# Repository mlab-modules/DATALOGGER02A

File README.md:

# DATALOGGER02A
<!--- LongName --->
## 
<!--- ELongName ---> 

<!--- Lead --->

<!--- ELead --->

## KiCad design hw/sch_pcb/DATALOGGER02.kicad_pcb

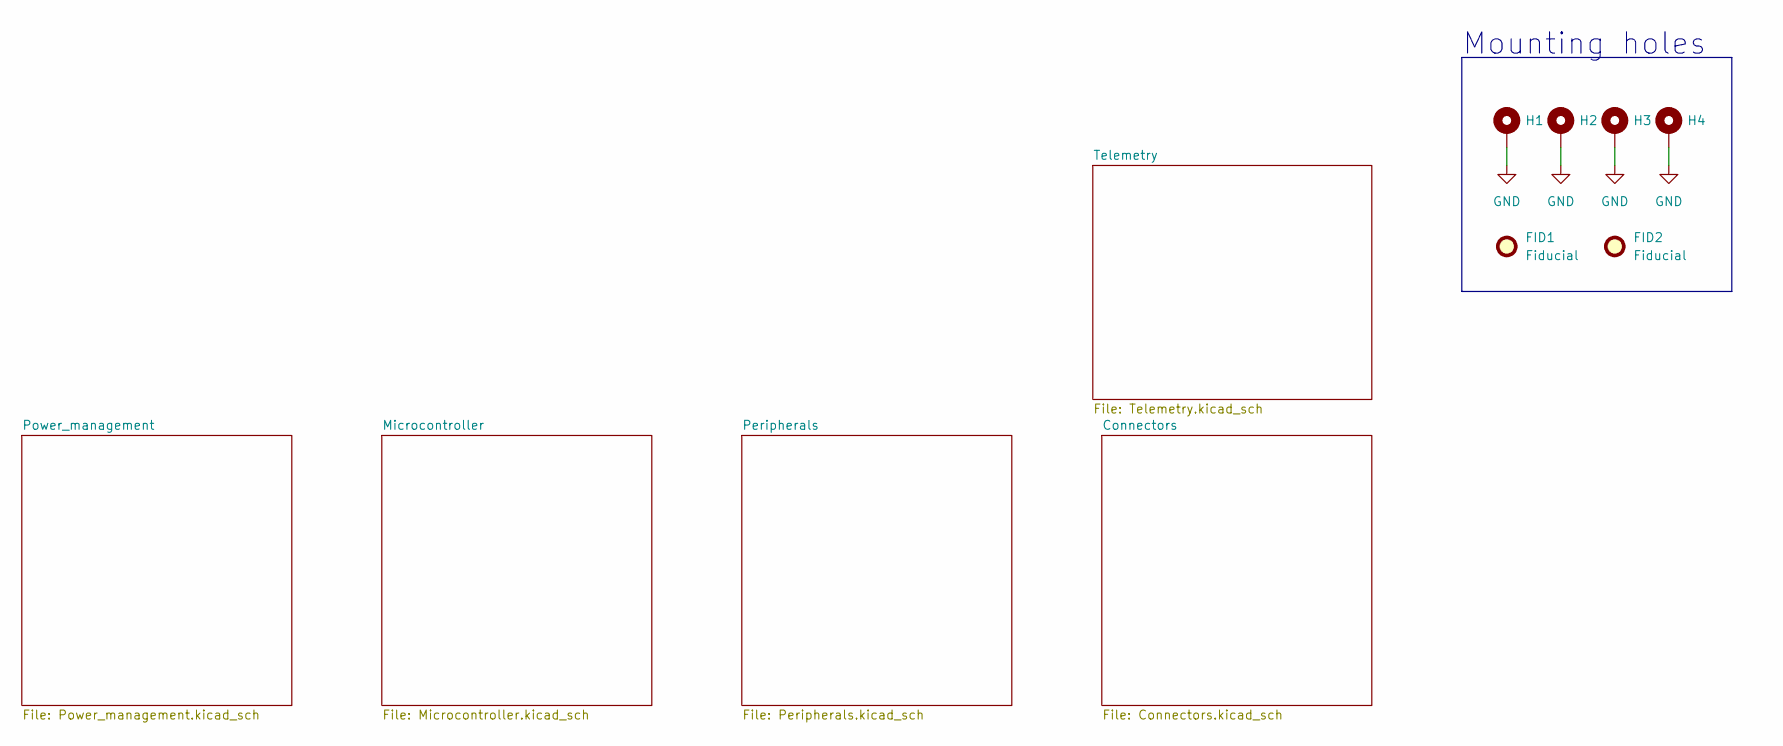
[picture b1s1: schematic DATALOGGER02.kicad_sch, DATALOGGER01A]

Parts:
FID1, FID2: Fiducial; Fiducial_1mm_Mask2mm
H1, H2, H3, H4: MountingHole_Pad; MountingHole_3mm

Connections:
GND: H1.1, H2.1, H3.1, H4.1; also elsewhere on the board

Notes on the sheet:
Mounting holes

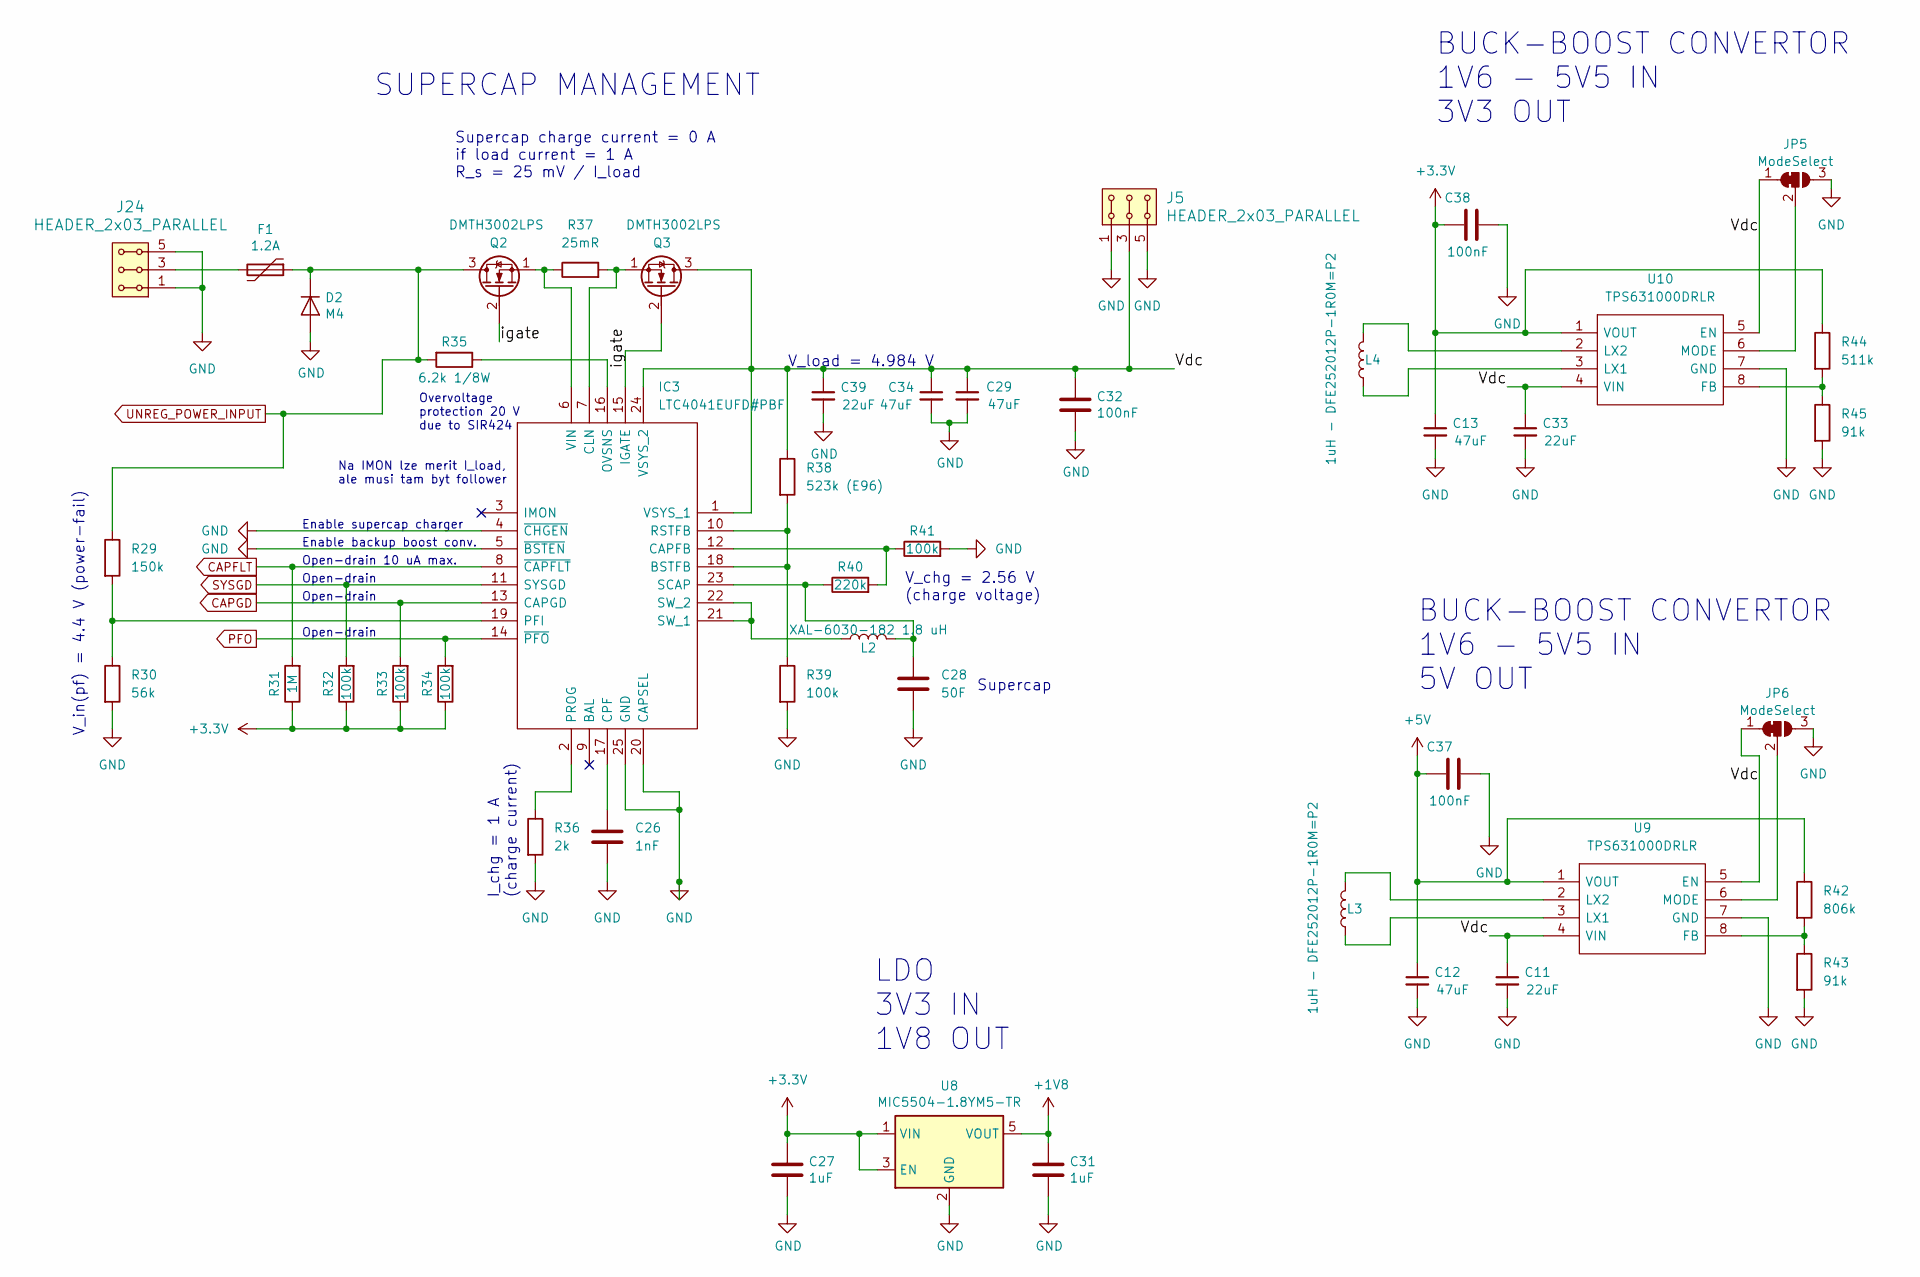
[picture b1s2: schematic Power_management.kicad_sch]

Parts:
C11, C33, C39: 22uF; C_0805_2012Metric
C12, C13, C29, C34: 47uF; C_0805_2012Metric
C26: 1nF; C_0805_2012Metric
C27, C31: 1uF; C_0805_2012Metric
C28: 50F; CP_Radial_D18.0mm_P7.50mm
C32, C37, C38: 100nF; C_0805_2012Metric
D2: M4; Diode-SMA_Standard
F1: 1.2A; 1812
IC3: LTC4041EUFD#PBF; QFN-24-1EP_4x5mm_P0.5mm_EP2.65x3.65mm; Mouser Part Number 584-4041EUFDPB
J5, J24: HEADER_2x03_PARALLEL; Straight_2x03
JP5, JP6: ModeSelect; SolderJumper-3_P1.3mm_Bridged12_RoundedPad1.0x1.5mm_NumberL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
L2: XAL-6030-182 1.8 uH; XAL6030181MEC
L3, L4: 1uH - DFE252012P-1R0M=P2; L_1008_2520Metric
Q2, Q3: DMTH3002LPS; D_POWERDI5060-8_6.0x5.1mm_P1.27mm; Manufacturer_Part_Number DMT31M7LPS-13
R29: 150k; R_0805_2012Metric
R30: 56k; R_0805_2012Metric
R31: 1M; R_0805_2012Metric
R32, R33, R34, R39, R41: 100k; R_0805_2012Metric
R35: 6.2k 1/8W; R_0805_2012Metric
R36: 2k; R_0805_2012Metric
R37: 25mR; R_0805_2012Metric
R38: 523k (E96); R_0805_2012Metric
R40: 220k; R_0805_2012Metric
R42: 806k; R_0805_2012Metric
R43, R45: 91k; R_0805_2012Metric
R44: 511k; R_0805_2012Metric
U8: MIC5504-1.8YM5-TR; SOT-23-5
U9, U10: TPS631000DRLR; SOT-583-8; Mouser Part Number 595-TPS631000DRLR

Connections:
+1V8: C31.1, U8.5 (VOUT); also elsewhere on the board
+3.3V: C13.1, C27.1, C38.1, R31.1, R32.1, R33.1, R34.1, R44.1, U8.1 (VIN), U8.3 (EN), U10.1 (VOUT); also elsewhere on the board
+5V: C12.1, C37.1, R42.1, U9.1 (VOUT); also elsewhere on the board
/Power_management/Vdc: C11.1, C29.1, C32.1, C33.1, C34.1, C39.1, IC3.1 (VSYS_1), IC3.24 (VSYS_2), J5.3, J5.4, JP5.1 (A), JP6.1 (A), Q3.3 (D), R38.1, U9.4 (VIN), U9.5 (EN), U10.4 (VIN), U10.5 (EN)
/Power_management/igate: IC3.15 (IGATE), Q2.2 (G), Q3.2 (G)
CAPFLT: IC3.8 (~CAPFLT), R31.2; also elsewhere on the board
CAPGD: IC3.13 (CAPGD), R33.2; also elsewhere on the board
GND: C11.2, C12.2, C13.2, C26.2, C27.2, C28.2, C29.2, C31.2, C32.2, C33.2, C34.2, C37.2, C38.2, C39.2, D2.2 (A), IC3.4 (~CHGEN), IC3.5 (~BSTEN), IC3.20 (CAPSEL), IC3.25 (GND), J5.1, J5.2, J5.5, J5.6, J24.1, J24.2, J24.5, J24.6, JP5.3 (B), JP6.3 (B), R30.2, R36.2, R39.2, R41.2, R43.2, R45.2, U8.2 (GND), U9.7 (GND), U10.7 (GND); also elsewhere on the board
unnamed: F1.2, J24.3, J24.4
unnamed: IC3.10 (RSTFB), IC3.18 (BSTFB), R38.2, R39.1
unnamed: IC3.12 (CAPFB), R40.2, R41.1
unnamed: IC3.7 (CLN), Q3.1 (S), R37.2
unnamed: C26.1, IC3.17 (CPF)
unnamed: IC3.16 (OVSNS), R35.1
unnamed: IC3.19 (PFI), R29.2, R30.1
unnamed: IC3.2 (PROG), R36.1
unnamed: C28.1, IC3.23 (SCAP), L2.2, R40.1
unnamed: IC3.21 (SW_1), IC3.22 (SW_2), L2.1
unnamed: IC3.6 (VIN), Q2.1 (S), R37.1
unnamed: JP5.2 (C), U10.6 (MODE)
unnamed: JP6.2 (C), U9.6 (MODE)
unnamed: R42.2, R43.1, U9.8 (FB)
unnamed: L3.1, U9.3 (LX1)
unnamed: L3.2, U9.2 (LX2)
unnamed: R44.2, R45.1, U10.8 (FB)
unnamed: L4.1, U10.3 (LX1)
unnamed: L4.2, U10.2 (LX2)
PFO: IC3.14 (~PFO), R34.2; also elsewhere on the board
SYSGD: IC3.11 (SYSGD), R32.2; also elsewhere on the board
UNREG_POWER_INPUT: D2.1 (K), F1.1, Q2.3 (D), R29.1, R35.2; also elsewhere on the board

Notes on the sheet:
Open-drain
V_chg = 2.56 V (charge voltage)
Open-drain 10 uA max.
Enable backup boost conv.
I_chg = 1 A (charge current)
Overvoltage protection 20 V due to SIR424
Supercap charge current = 0 A if load current = 1 A R_s = 25 mV / I_load
LDO 3V3 IN 1V8 OUT
BUCK-BOOST CONVERTOR 1V6 - 5V5 IN 5V OUT
Supercap
Na IMON lze merit I_load, ale musi tam byt follower
SUPERCAP MANAGEMENT
Enable supercap charger
V_load = 4.984 V
V_in(pf) = 4.4 V (power-fail)
BUCK-BOOST CONVERTOR 1V6 - 5V5 IN 3V3 OUT

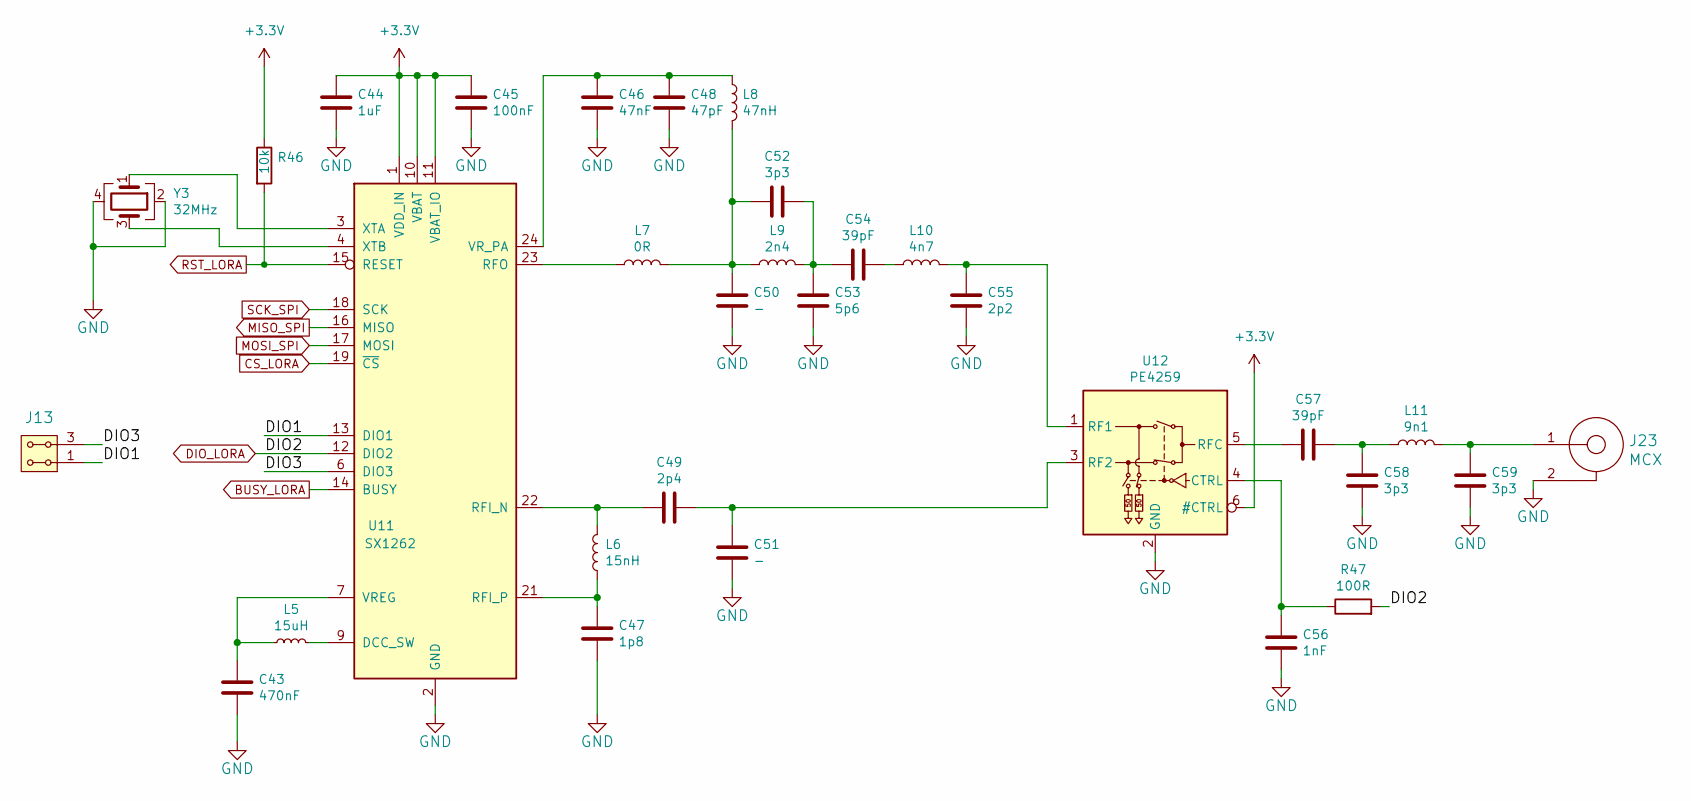
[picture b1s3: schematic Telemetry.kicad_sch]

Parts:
C43: 470nF; C_0805_2012Metric
C44: 1uF; C_0805_2012Metric
C45: 100nF; C_0805_2012Metric
C46: 47nF; C_0805_2012Metric
C47: 1p8; C_0603_1608Metric
C48: 47pF; C_0805_2012Metric
C49: 2p4; C_0603_1608Metric
C50, C51: -; C_0603_1608Metric
C52, C58, C59: 3p3; C_0603_1608Metric
C53: 5p6; C_0603_1608Metric
C54, C57: 39pF; C_0603_1608Metric
C55: 2p2; C_0603_1608Metric
C56: 1nF; C_0805_2012Metric
J13: HEADER_2x02_PARALLEL; Straight_2x02
J23: MCX
L5: 15uH; L_0805_2012Metric
L6: 15nH; L_0603_1608Metric
L7: 0R; L_0603_1608Metric
L8: 47nH; L_0603_1608Metric
L9: 2n4; L_0603_1608Metric
L10: 4n7; L_0603_1608Metric
L11: 9n1; L_0603_1608Metric
R46: 10k; R_0805_2012Metric
R47: 100R; R_0805_2012Metric
U11: SX1262; QFN-24-1EP_4x4mm_P0.5mm_EP2.6x2.6mm_ThermalVias
U12: PE4259; SOT-363_SC-70-6
Y3: 32MHz; Crystal_SMD_NX2016SA

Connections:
+3.3V: C44.1, C45.1, R46.1, U11.1 (VDD_IN), U11.10 (VBAT), U11.11 (VBAT_IO), U12.6 (#CTRL); also elsewhere on the board
/Telemetry/DIO1: J13.1, J13.2, U11.13 (DIO1)
/Telemetry/DIO3: J13.3, J13.4, U11.6 (DIO3)
BUSY_LORA: U11.14 (BUSY); also elsewhere on the board
CS_LORA: U11.19 (~CS); also elsewhere on the board
DIO_LORA: R47.2, U11.12 (DIO2); also elsewhere on the board
GND: C43.2, C44.2, C45.2, C46.2, C47.2, C48.2, C50.2, C51.2, C53.2, C55.2, C56.2, C58.1, C59.1, J23.2, U11.2 (GND), U11.5 (GND), U11.8 (GND), U11.20 (GND), U11.25 (GND), U12.2 (GND), Y3.2, Y3.4; also elsewhere on the board
MISO_SPI: U11.16 (MISO); also elsewhere on the board
MOSI_SPI: U11.17 (MOSI); also elsewhere on the board
unnamed: C50.1, C52.2, L7.2, L8.2, L9.1
unnamed: C52.1, C53.1, C54.2, L9.2
unnamed: C54.1, L10.1
unnamed: C57.1, C58.2, L11.1
unnamed: C59.2, J23.1, L11.2
unnamed: L5.2, U11.9 (DCC_SW)
unnamed: C49.2, L6.2, U11.22 (RFI_N)
unnamed: C47.1, L6.1, U11.21 (RFI_P)
unnamed: L7.1, U11.23 (RFO)
unnamed: C43.1, L5.1, U11.7 (VREG)
unnamed: C46.1, C48.1, L8.1, U11.24 (VR_PA)
unnamed: U11.3 (XTA), Y3.1
unnamed: U11.4 (XTB), Y3.3
unnamed: C56.1, R47.1, U12.4 (CTRL)
unnamed: C55.1, L10.2, U12.1 (RF1)
unnamed: C49.1, C51.1, U12.3 (RF2)
unnamed: C57.2, U12.5 (RFC)
RST_LORA: R46.2, U11.15 (RESET); also elsewhere on the board
SCK_SPI: U11.18 (SCK); also elsewhere on the board

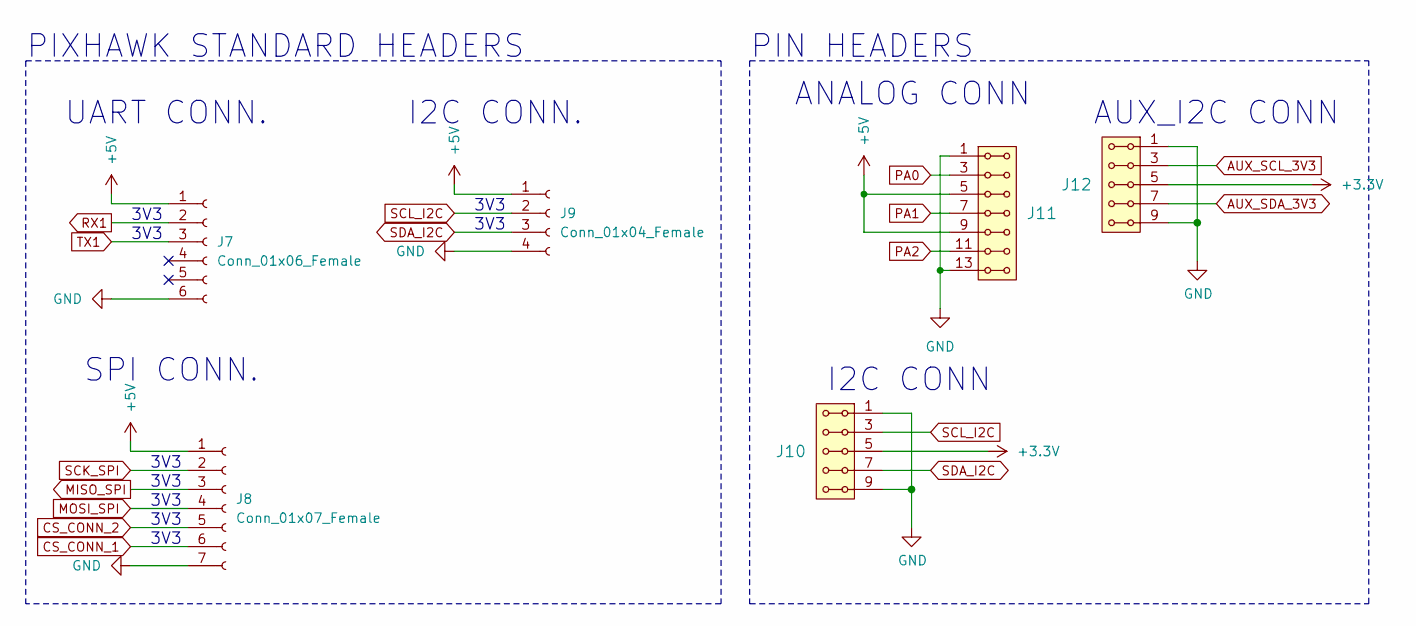
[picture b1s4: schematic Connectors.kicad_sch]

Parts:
J7: Conn_01x06_Female; JST_GH_SM06B-GHS-TB_1x06-1MP_P1.25mm_Horizontal
J8: Conn_01x07_Female; JST_GH_SM07B-GHS-TB_1x07-1MP_P1.25mm_Horizontal
J9: Conn_01x04_Female; JST_GH_SM04B-GHS-TB_1x04-1MP_P1.25mm_Horizontal
J10, J12: HEADER_2x05_PARALLEL; Straight_2x05
J11: HEADER_2x07_PARALLEL; Straight_2x07

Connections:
+3.3V: J10.5, J10.6, J12.5, J12.6; also elsewhere on the board
+5V: J7.1, J8.1, J9.1, J11.5, J11.6, J11.9, J11.10; also elsewhere on the board
AUX_SCL_3V3: J12.3, J12.4; also elsewhere on the board
AUX_SDA_3V3: J12.7, J12.8; also elsewhere on the board
CS_CONN_1: J8.6; also elsewhere on the board
CS_CONN_2: J8.5; also elsewhere on the board
GND: J7.6, J8.7, J9.4, J10.1, J10.2, J10.9, J10.10, J11.1, J11.2, J11.13, J11.14, J12.1, J12.2, J12.9, J12.10; also elsewhere on the board
MISO_SPI: J8.3; also elsewhere on the board
MOSI_SPI: J8.4; also elsewhere on the board
PA0: J11.3, J11.4; also elsewhere on the board
PA1: J11.7, J11.8; also elsewhere on the board
PA2: J11.11, J11.12; also elsewhere on the board
RX1: J7.2; also elsewhere on the board
SCK_SPI: J8.2; also elsewhere on the board
SCL_I2C: J9.2, J10.3, J10.4; also elsewhere on the board
SDA_I2C: J9.3, J10.7, J10.8; also elsewhere on the board
TX1: J7.3; also elsewhere on the board

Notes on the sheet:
3V3
ANALOG CONN
I2C CONN
I2C CONN.
AUX_I2C CONN
PIN HEADERS
SPI CONN.
UART CONN.
PIXHAWK STANDARD HEADERS

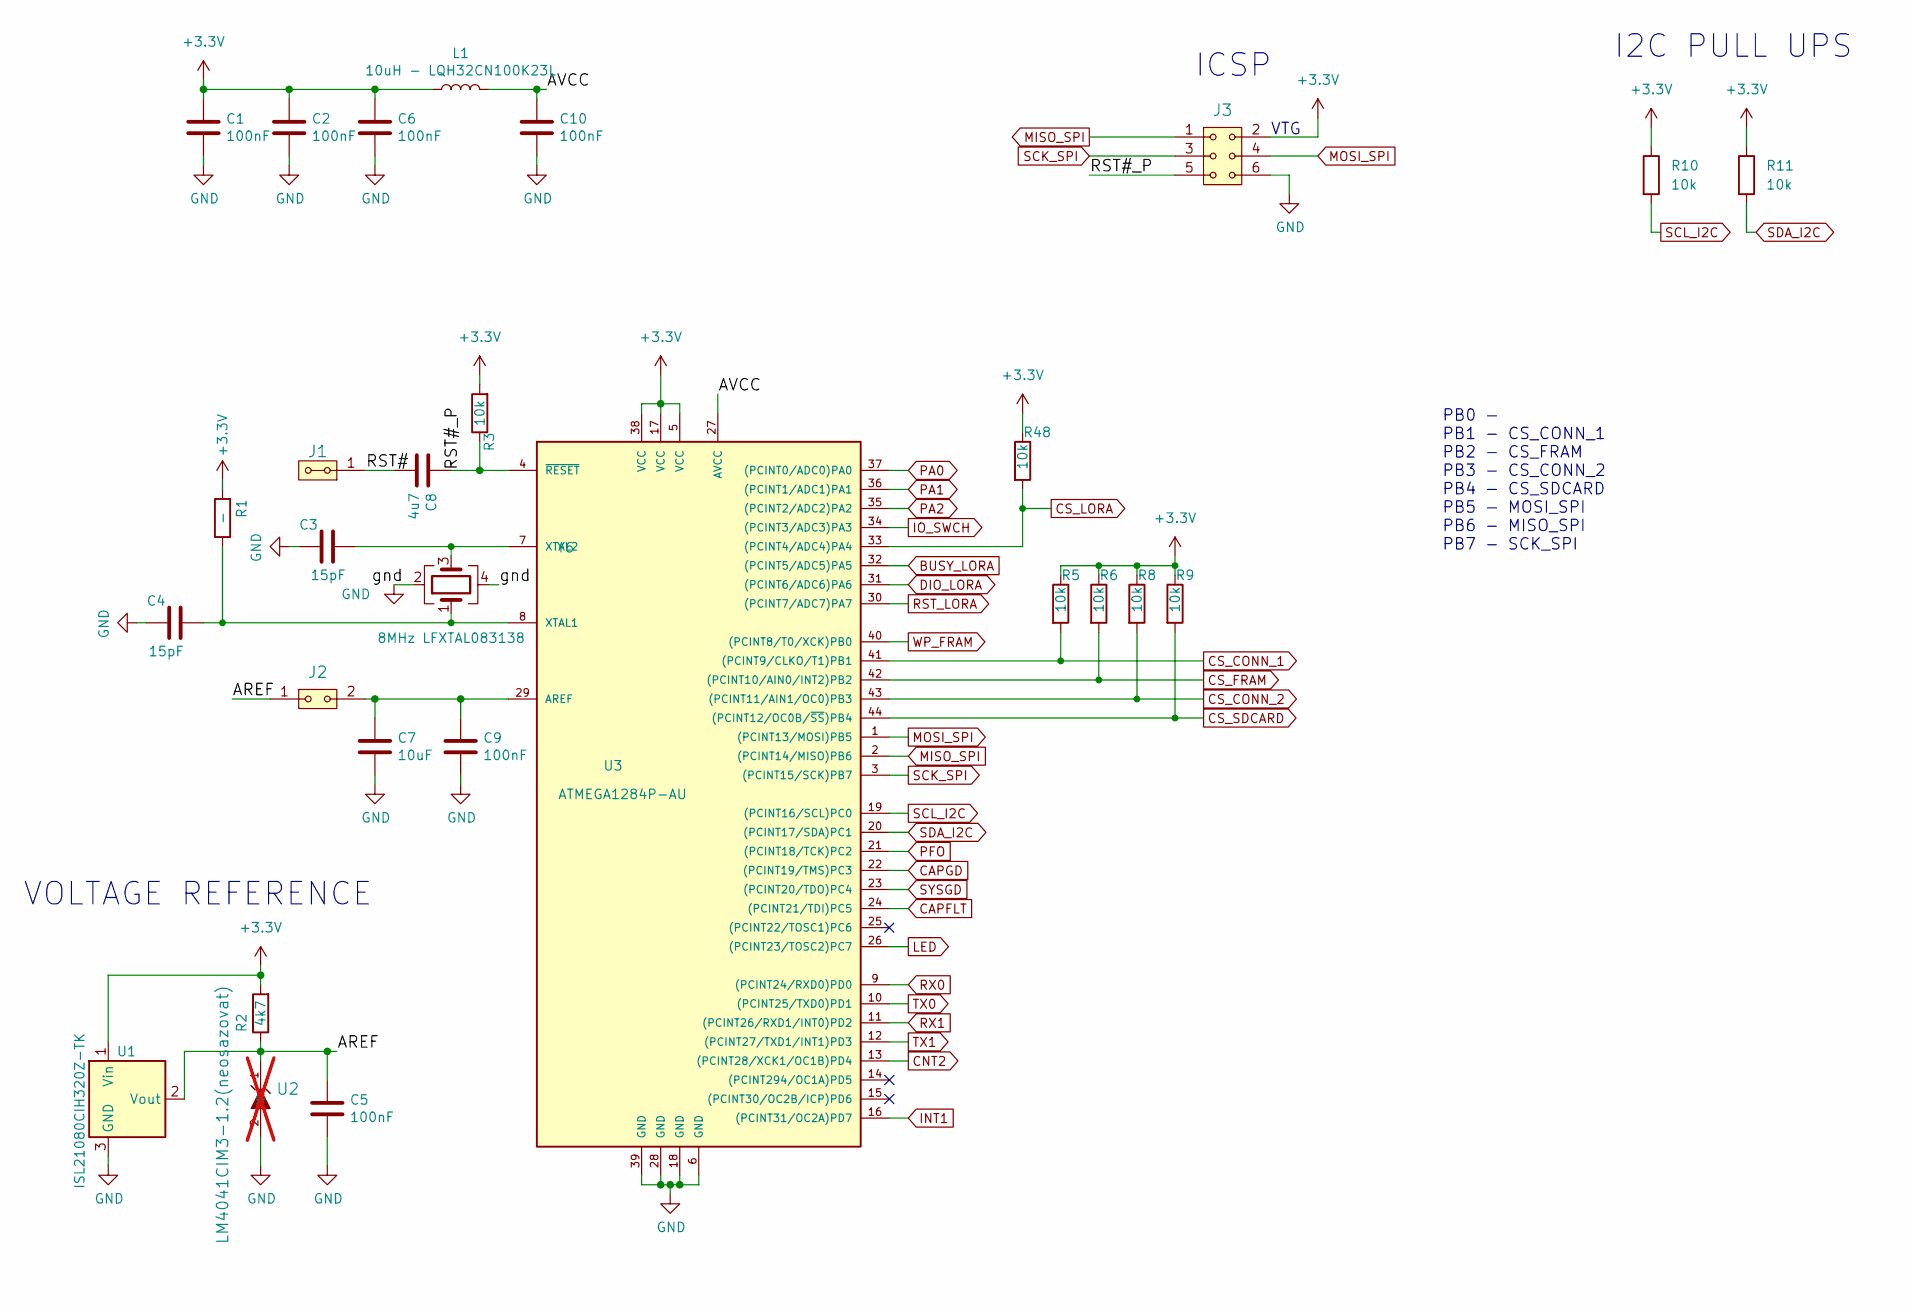
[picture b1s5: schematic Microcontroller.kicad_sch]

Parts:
C1, C2, C5, C6, C9, C10: 100nF; C_0805_2012Metric
C3, C4: 15pF; C_0805_2012Metric
C7: 10uF; C_0805_2012Metric
C8: 4u7; C_0805_2012Metric
J1: HEADER_2x01_PARALLEL; Straight_2x01
J2: HEADER_2x01; Straight_2x01
J3: HEADER_2x03; Straight_2x03
L1: 10uH - LQH32CN100K23L; SMD-1210
R1: -; R_0805_2012Metric
R2: 4k7; R_0805_2012Metric
R3, R5, R6, R8, R9, R10, R11, R48: 10k; R_0805_2012Metric
U1: ISL21080CIH320Z-TK; SOT-23
U2: LM4041CIM3-1.2(neosazovat); SOT-23; not fitted
U3: ATMEGA1284P-AU; TQFP-44_10x10mm_P0.8mm
Y6: 8MHz LFXTAL083138; Crystal SMD CFPX-180

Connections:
+3.3V: C1.1, C2.1, C6.1, J3.2, L1.1, R1.2, R2.2, R3.2, R5.1, R6.1, R8.1, R9.1, R10.1, R11.1, R48.1, U1.1 (Vin), U3.5 (VCC), U3.17 (VCC), U3.38 (VCC); also elsewhere on the board
/Microcontroller/AREF: C5.1, J2.1, R2.1, U1.2 (Vout), U2.1 (K)
/Microcontroller/AVCC: C10.1, L1.2, U3.27 (AVCC)
/Microcontroller/RST#: C8.2, J1.1, J1.2
/Microcontroller/RST#_P: C8.1, J3.5, R3.1, U3.4 (~RESET)
BUSY_LORA: U3.32 ((PCINT5/ADC5)PA5); also elsewhere on the board
CAPFLT: U3.24 ((PCINT21/TDI)PC5); also elsewhere on the board
CAPGD: U3.22 ((PCINT19/TMS)PC3); also elsewhere on the board
CNT2: U3.13 ((PCINT28/XCK1/OC1B)PD4); also elsewhere on the board
CS_CONN_1: R5.2, U3.41 ((PCINT9/CLKO/T1)PB1); also elsewhere on the board
CS_CONN_2: R8.2, U3.43 ((PCINT11/AIN1/OC0)PB3); also elsewhere on the board
CS_FRAM: R6.2, U3.42 ((PCINT10/AIN0/INT2)PB2); also elsewhere on the board
CS_LORA: R48.2, U3.33 ((PCINT4/ADC4)PA4); also elsewhere on the board
CS_SDCARD: R9.2, U3.44 ((PCINT12/OC0B/~SS)PB4); also elsewhere on the board
DIO_LORA: U3.31 ((PCINT6/ADC6)PA6); also elsewhere on the board
GND: C1.2, C2.2, C3.1, C4.1, C5.2, C6.2, C7.2, C9.2, C10.2, J3.6, U1.3 (GND), U2.2 (A), U3.6 (GND), U3.18 (GND), U3.28 (GND), U3.39 (GND), Y6.2, Y6.4; also elsewhere on the board
INT1: U3.16 ((PCINT31/OC2A)PD7); also elsewhere on the board
IO_SWCH: U3.34 ((PCINT3/ADC3)PA3); also elsewhere on the board
LED: U3.26 ((PCINT23/TOSC2)PC7); also elsewhere on the board
MISO_SPI: J3.1, U3.2 ((PCINT14/MISO)PB6); also elsewhere on the board
MOSI_SPI: J3.4, U3.1 ((PCINT13/MOSI)PB5); also elsewhere on the board
unnamed: C7.1, C9.1, J2.2, U3.29 (AREF)
unnamed: C4.2, R1.1, U3.8 (XTAL1), Y6.1
unnamed: C3.2, U3.7 (XTAL2), Y6.3
PA0: U3.37 ((PCINT0/ADC0)PA0); also elsewhere on the board
PA1: U3.36 ((PCINT1/ADC1)PA1); also elsewhere on the board
PA2: U3.35 ((PCINT2/ADC2)PA2); also elsewhere on the board
PFO: U3.21 ((PCINT18/TCK)PC2); also elsewhere on the board
RST_LORA: U3.30 ((PCINT7/ADC7)PA7); also elsewhere on the board
RX0: U3.9 ((PCINT24/RXD0)PD0)
RX1: U3.11 ((PCINT26/RXD1/INT0)PD2); also elsewhere on the board
SCK_SPI: J3.3, U3.3 ((PCINT15/SCK)PB7); also elsewhere on the board
SCL_I2C: R10.2, U3.19 ((PCINT16/SCL)PC0); also elsewhere on the board
SDA_I2C: R11.2, U3.20 ((PCINT17/SDA)PC1); also elsewhere on the board
SYSGD: U3.23 ((PCINT20/TDO)PC4); also elsewhere on the board
TX0: U3.10 ((PCINT25/TXD0)PD1)
TX1: U3.12 ((PCINT27/TXD1/INT1)PD3); also elsewhere on the board
WP_FRAM: U3.40 ((PCINT8/T0/XCK)PB0); also elsewhere on the board

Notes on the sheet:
VOLTAGE REFERENCE
I2C PULL UPS
ICSP
VTG
PB0 - PB1 - CS_CONN_1 PB2 - CS_FRAM PB3 - CS_CONN_2 PB4 - CS_SDCARD PB5 - MOSI_SPI PB6 - MISO_SPI PB7 - SCK_SPI

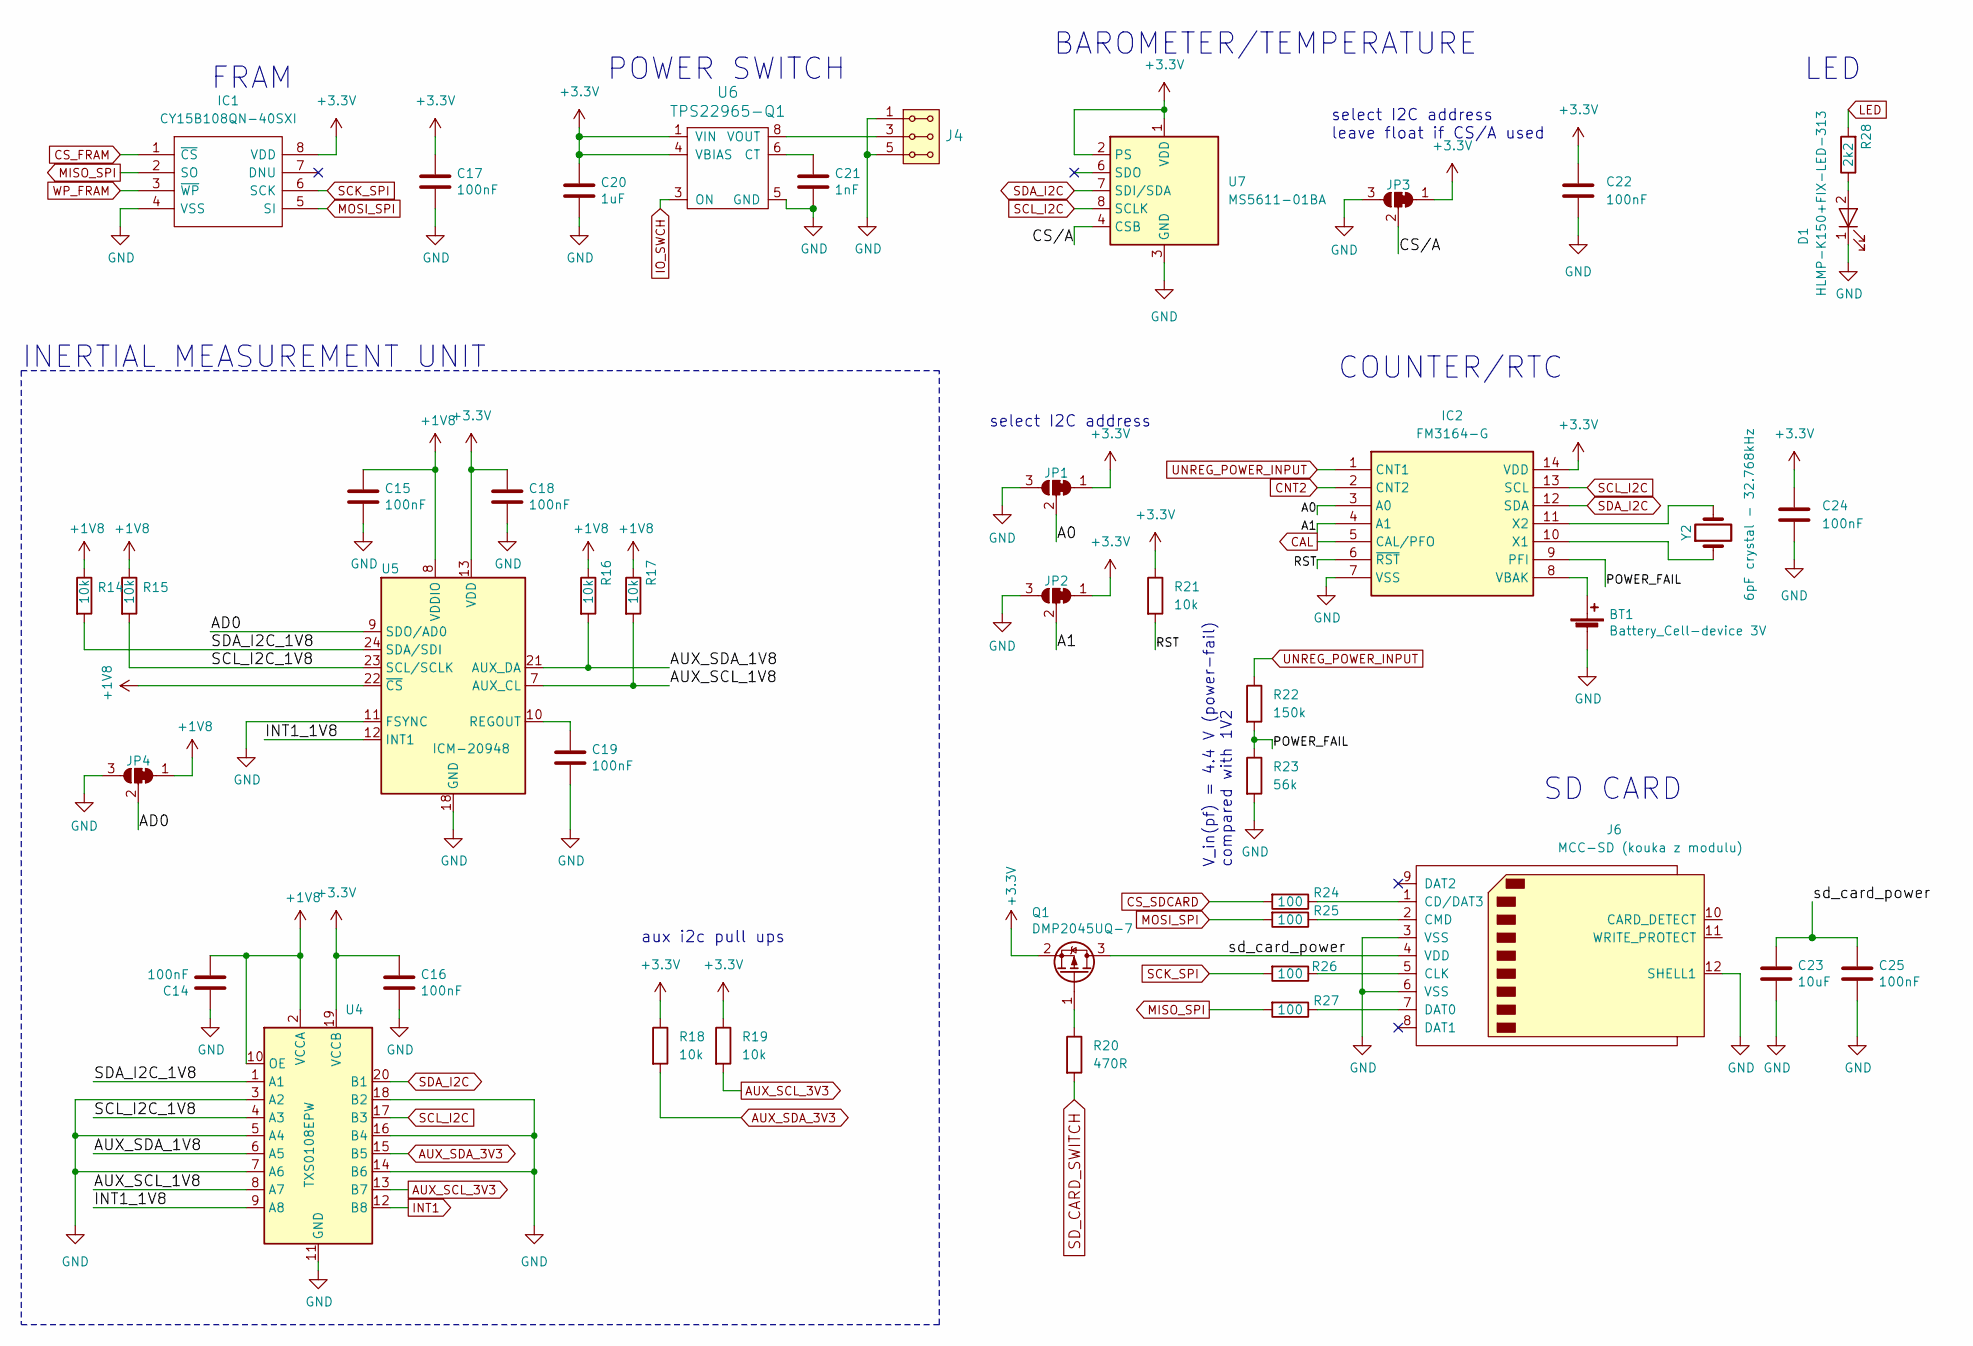
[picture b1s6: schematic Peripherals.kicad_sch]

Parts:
BT1: Battery_Cell-device 3V; BatteryHolder_Keystone_2998_1x6.8mm
C14, C15, C16, C17, C18, C19, C22, C24, C25: 100nF; C_0805_2012Metric
C20: 1uF; C_0805_2012Metric
C21: 1nF; C_0805_2012Metric
C23: 10uF; C_0805_2012Metric
D1: HLMP-K150+FIX-LED-313; LED_1206_mill
IC1: CY15B108QN-40SXI; SOIC-8_3.9x4.9mm_Pitch1.27mm; Mouser Part Number 727-CY15B108QN-40SXI
IC2: FM3164-G; SOIC-14_3.9x8.7mm_P1.27mm; Manufacturer_Part_Number FM3164-S
J4: HEADER_2x03_PARALLEL; Straight_2x03
J6: MCC-SD (kouka z modulu); MCC-SD
JP1, JP2, JP3, JP4: SolderJumper_3_Bridged12; SolderJumper-3_P1.3mm_Bridged12_RoundedPad1.0x1.5mm_NumberL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
Q1: DMP2045UQ-7; SOT-23
R14, R15, R16, R17, R18, R19, R21: 10k; R_0805_2012Metric
R20: 470R; R_0805_2012Metric
R22: 150k; R_0805_2012Metric
R23: 56k; R_0805_2012Metric
R24, R25, R26, R27: 100; R_0805_2012Metric
R28: 2k2; R_0805_2012Metric
U4: TXS0108EPW; TSSOP-20_4.4x6.5mm_P0.65mm
U5: ICM-20948; InvenSense_QFN-24_3x3mm_P0.4mm
U6: TPS22965-Q1; WSON-8-1EP_2x2mm_P0.5mm_EP0.9x1.6mm_ThermalVias
U7: MS5611-01BA; LGA-8_3x5mm_P1.25mm
Y2: 6pF crystal - 32.768kHz; ABS07

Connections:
+1V8: C14.2, C15.1, JP4.1 (A), R14.1, R15.1, R16.1, R17.1, U4.2 (VCCA), U4.10 (OE), U5.8 (VDDIO), U5.22 (~CS); also elsewhere on the board
+3.3V: C16.1, C17.1, C18.1, C20.1, C22.1, C24.1, IC1.8 (VDD), IC2.14 (VDD), JP1.1 (A), JP2.1 (A), JP3.1 (A), Q1.2 (S), R18.1, R19.1, R21.1, U4.19 (VCCB), U5.13 (VDD), U6.1 (VIN), U6.2 (VIN), U6.4 (VBIAS), U7.1 (VDD), U7.2 (PS); also elsewhere on the board
/Peripherals/A0: IC2.3 (A0), JP1.2 (C)
/Peripherals/A1: IC2.4 (A1), JP2.2 (C)
/Peripherals/AD0: JP4.2 (C), U5.9 (SDO/AD0)
/Peripherals/AUX_SCL_1V8: R17.2, U4.8 (A7), U5.7 (AUX_CL)
/Peripherals/AUX_SDA_1V8: R16.2, U4.6 (A5), U5.21 (AUX_DA)
/Peripherals/CS/A: JP3.2 (C), U7.4 (CSB), U7.5 (CSB)
/Peripherals/INT1_1V8: U4.9 (A8), U5.12 (INT1)
/Peripherals/POWER_FAIL: IC2.9 (PFI), R22.2, R23.1
/Peripherals/RST: IC2.6 (~RST), R21.2
/Peripherals/SCL_I2C_1V8: R15.2, U4.4 (A3), U5.23 (SCL/SCLK)
/Peripherals/SDA_I2C_1V8: R14.2, U4.1 (A1), U5.24 (SDA/SDI)
/Peripherals/sd_card_power: C23.1, C25.1, J6.4 (VDD), Q1.3 (D)
AUX_SCL_3V3: R19.2, U4.13 (B7); also elsewhere on the board
AUX_SDA_3V3: R18.2, U4.15 (B5); also elsewhere on the board
CAL: IC2.5 (CAL/PFO)
CNT2: IC2.2 (CNT2); also elsewhere on the board
CS_FRAM: IC1.1 (~CS); also elsewhere on the board
CS_SDCARD: R24.2; also elsewhere on the board
GND: BT1.2 (-), C14.1, C15.2, C16.2, C17.2, C18.2, C19.2, C20.2, C21.2, C22.2, C23.2, C24.2, C25.2, D1.1 (K), IC1.4 (VSS), IC2.7 (VSS), J4.1, J4.2, J4.5, J4.6, J6.3 (VSS), J6.6 (VSS), J6.12 (SHELL1), JP1.3 (B), JP2.3 (B), JP3.3 (B), JP4.3 (B), R23.2, U4.3 (A2), U4.5 (A4), U4.7 (A6), U4.11 (GND), U4.14 (B6), U4.16 (B4), U4.18 (B2), U5.11 (FSYNC), U5.18 (GND), U5.20 (GND), U6.5 (GND), U6.9, U7.3 (GND); also elsewhere on the board
INT1: U4.12 (B8); also elsewhere on the board
IO_SWCH: U6.3 (ON); also elsewhere on the board
LED: R28.2; also elsewhere on the board
MISO_SPI: IC1.2 (SO), R27.2; also elsewhere on the board
MOSI_SPI: IC1.5 (SI), R25.2; also elsewhere on the board
unnamed: BT1.1 (+), IC2.8 (VBAK)
unnamed: D1.2 (A), R28.1
unnamed: IC2.10 (X1), Y2.1
unnamed: IC2.11 (X2), Y2.2
unnamed: J4.3, J4.4, U6.7 (VOUT), U6.8 (VOUT)
unnamed: J6.1 (CD/DAT3), R24.1
unnamed: J6.5 (CLK), R26.1
unnamed: J6.2 (CMD), R25.1
unnamed: J6.7 (DAT0), R27.1
unnamed: Q1.1 (G), R20.1
unnamed: C19.1, U5.10 (REGOUT)
unnamed: C21.1, U6.6 (CT)
SCK_SPI: IC1.6 (SCK), R26.2; also elsewhere on the board
SCL_I2C: IC2.13 (SCL), U4.17 (B3), U7.8 (SCLK); also elsewhere on the board
SDA_I2C: IC2.12 (SDA), U4.20 (B1), U7.7 (SDI/SDA); also elsewhere on the board
SD_CARD_SWITCH: R20.2
UNREG_POWER_INPUT: IC2.1 (CNT1), R22.1; also elsewhere on the board
WP_FRAM: IC1.3 (~WP); also elsewhere on the board

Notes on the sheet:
select I2C address
POWER SWITCH
COUNTER/RTC
INERTIAL MEASUREMENT UNIT
FRAM
V_in(pf) = 4.4 V (power-fail) compared with 1V2
SD CARD
aux i2c pull ups
BAROMETER/TEMPERATURE
select I2C address leave float if CS/A used
LED

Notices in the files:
hw/sch_pcb/DATALOGGER02.kicad_pcb:
GPL 3.0
